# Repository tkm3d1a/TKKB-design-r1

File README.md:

# TKKB-design-r1
 TKm3d1a Keyboard design project, revision 1

MY first attempt at using Github for rev control and publishing of any/all files in KB design.

The Goal is a 60% ish keyboard design, no multiple layout support.  Exposed diodes, with a swapable MCU.

Possibly also add numpad support as I personally use the numpad often.  

Designed to use PCB mount MX style switches.

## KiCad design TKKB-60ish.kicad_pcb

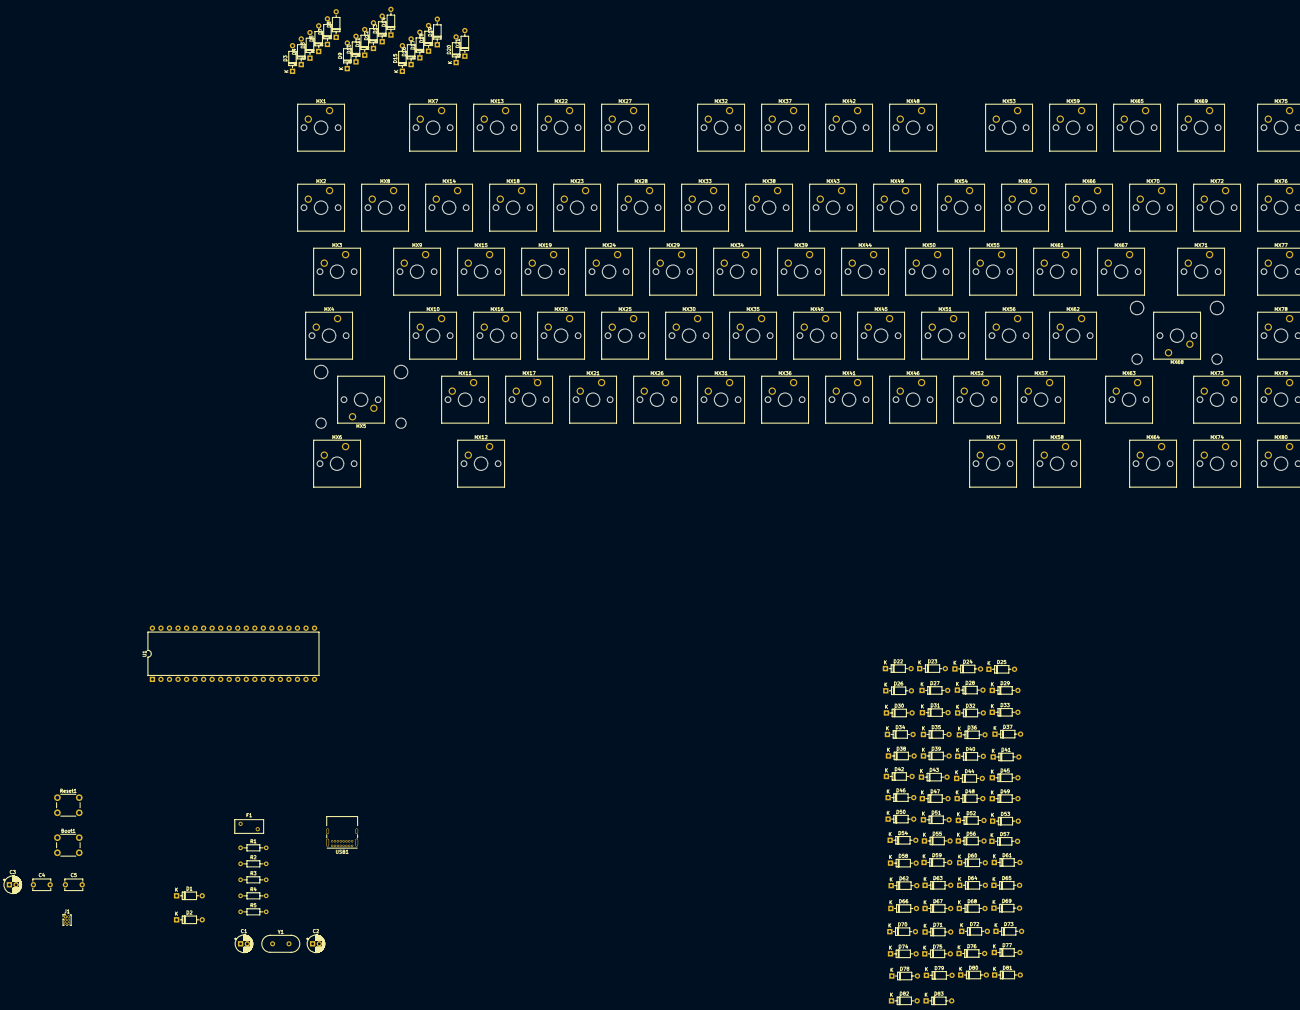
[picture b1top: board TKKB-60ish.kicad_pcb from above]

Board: 2 copper layers, 180 parts (0 on the bottom side), 116 nets.

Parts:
Boot1: Boot; SW_PUSH_6mm
C1, C2: 22p; CP_Radial_D5.0mm_P2.00mm
C3: 4u7; CP_Radial_D5.0mm_P2.00mm
C4, C5: 0u1; C_Disc_D5.1mm_W3.2mm_P5.00mm
D1, D2: 3.6V; D_DO-35_SOD27_P7.62mm_Horizontal
D3, D4, D5, D6, D7, D8, D9, D10, D11, D12, D13, D14, D15, D16, D17, D18, D19, D20, D21, D22, D23, D24, D25, D26, D27, D28, D29, D30, D31, D32, D33, D34, D35, D36, D37, D38, D39, D40, D41, D42, D43, D44, D45, D46, D47, D48, D49, D50, D51, D52, D53, D54, D55, D56, D57, D58, D59, D60, D61, D62, D63, D64, D65, D66, D67, D68, D69, D70, D71, D72, D73, D74, D75, D76, D77, D78, D79, D80, D81, D82, D83: 1N4148TR; D_DO-35_SOD27_P7.62mm_Horizontal
F1: 500mA; Fuse_BelFuse_0ZRE0005FF_L8.3mm_W3.8mm
J1: AVR-ISP-6; PinHeader_2x03_P1.00mm_Vertical
MX1: Esc; SW_Cherry_MX_1.00u_PCB
MX2: Tilde; SW_Cherry_MX_1.00u_PCB
MX3: Tab; SW_Cherry_MX_1.50u_PCB
MX4: Step Caps; SW_Cherry_MX_1.00u_PCB
MX5: Shift; SW_Cherry_MX_2.25u_PCB
MX6: Ctrl; SW_Cherry_MX_1.50u_PCB
MX7: F1; SW_Cherry_MX_1.00u_PCB
MX8: 1; SW_Cherry_MX_1.00u_PCB
MX9: Q; SW_Cherry_MX_1.00u_PCB
MX10: A; SW_Cherry_MX_1.00u_PCB
MX11: Z; SW_Cherry_MX_1.00u_PCB
MX12: Alt; SW_Cherry_MX_1.00u_PCB
MX13: F2; SW_Cherry_MX_1.00u_PCB
MX14: 2; SW_Cherry_MX_1.00u_PCB
MX15: W; SW_Cherry_MX_1.00u_PCB
MX16: S; SW_Cherry_MX_1.00u_PCB
MX17: X; SW_Cherry_MX_1.00u_PCB
MX18: 3; SW_Cherry_MX_1.00u_PCB
MX19: E; SW_Cherry_MX_1.00u_PCB
MX20: D; SW_Cherry_MX_1.00u_PCB
MX21: C; SW_Cherry_MX_1.00u_PCB
MX22: F3; SW_Cherry_MX_1.00u_PCB
MX23: 4; SW_Cherry_MX_1.00u_PCB
MX24: R; SW_Cherry_MX_1.00u_PCB
MX25: F; SW_Cherry_MX_1.00u_PCB
MX26: V; SW_Cherry_MX_1.00u_PCB
MX27: F4; SW_Cherry_MX_1.00u_PCB
MX28: 5; SW_Cherry_MX_1.00u_PCB
MX29: T; SW_Cherry_MX_1.00u_PCB
MX30: G; SW_Cherry_MX_1.00u_PCB
MX31: B; SW_Cherry_MX_1.00u_PCB
MX32: F5; SW_Cherry_MX_1.00u_PCB
MX33: 6; SW_Cherry_MX_1.00u_PCB
MX34: Y; SW_Cherry_MX_1.00u_PCB
MX35: H; SW_Cherry_MX_1.00u_PCB
MX36: N; SW_Cherry_MX_1.00u_PCB
MX37: F6; SW_Cherry_MX_1.00u_PCB
MX38: 7; SW_Cherry_MX_1.00u_PCB
MX39: U; SW_Cherry_MX_1.00u_PCB
MX40: J; SW_Cherry_MX_1.00u_PCB
MX41: M; SW_Cherry_MX_1.00u_PCB
MX42: F7; SW_Cherry_MX_1.00u_PCB
MX43: 8; SW_Cherry_MX_1.00u_PCB
MX44: I; SW_Cherry_MX_1.00u_PCB
MX45: K; SW_Cherry_MX_1.00u_PCB
MX46: <; SW_Cherry_MX_1.00u_PCB
MX47: R Alt; SW_Cherry_MX_1.00u_PCB
MX48: F8; SW_Cherry_MX_1.00u_PCB
MX49: 9; SW_Cherry_MX_1.00u_PCB
MX50: O; SW_Cherry_MX_1.00u_PCB
MX51: L; SW_Cherry_MX_1.00u_PCB
MX52: >; SW_Cherry_MX_1.00u_PCB
MX53: F9; SW_Cherry_MX_1.00u_PCB
MX54: 0; SW_Cherry_MX_1.00u_PCB
MX55: P; SW_Cherry_MX_1.00u_PCB
MX56: ;; SW_Cherry_MX_1.00u_PCB
MX57: /; SW_Cherry_MX_1.00u_PCB
MX58: R Ctrl; SW_Cherry_MX_1.00u_PCB
MX59: F10; SW_Cherry_MX_1.00u_PCB
MX60: -; SW_Cherry_MX_1.00u_PCB
MX61: [; SW_Cherry_MX_1.00u_PCB
MX62: '; SW_Cherry_MX_1.00u_PCB
MX63: RShift; SW_Cherry_MX_1.75u_PCB
MX64: Left Arrow; SW_Cherry_MX_1.00u_PCB
MX65: F11; SW_Cherry_MX_1.00u_PCB
MX66: =; SW_Cherry_MX_1.00u_PCB
MX67: ]; SW_Cherry_MX_1.00u_PCB
MX68: Enter; SW_Cherry_MX_2.25u_PCB
MX69: F12; SW_Cherry_MX_1.00u_PCB
MX70: \; SW_Cherry_MX_1.00u_PCB
MX71: bACKSPACE; SW_Cherry_MX_1.50u_PCB
MX72: Del; SW_Cherry_MX_1.00u_PCB
MX73: Up Arrow; SW_Cherry_MX_1.00u_PCB
MX74: Down Arrow; SW_Cherry_MX_1.00u_PCB
MX75: ?; SW_Cherry_MX_1.00u_PCB
MX76: Home; SW_Cherry_MX_1.00u_PCB
MX77: PgUp; SW_Cherry_MX_1.00u_PCB
MX78: PgDn; SW_Cherry_MX_1.00u_PCB
MX79: End; SW_Cherry_MX_1.00u_PCB
MX80: Right Arrow; SW_Cherry_MX_1.00u_PCB
R1, R2: 5k1; R_Axial_DIN0204_L3.6mm_D1.6mm_P7.62mm_Horizontal
R3: 10k; R_Axial_DIN0204_L3.6mm_D1.6mm_P7.62mm_Horizontal
R4, R5: 75R; R_Axial_DIN0204_L3.6mm_D1.6mm_P7.62mm_Horizontal
Reset1: Reset; SW_PUSH_6mm
U1: ATmega32A-PU; DIP-40_W15.24mm
USB1: Type-C_USB_C_GCT_USB4085; USB_C_Receptacle_GCT_USB4085
Y1: 16MHz; Crystal_HC49-U_Vertical

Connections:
+5V: C3.1, C4.1, C5.1, F1.1, J1.2, R3.1, U1.10, U1.30
/Keyboard Matrix/Col_0: MX1.1, MX2.1, MX3.1, MX4.1, MX5.1, MX6.1, MX7.1, MX8.1, MX9.1, MX10.1, MX11.1, MX12.1
/Keyboard Matrix/Col_1: MX13.1, MX14.1, MX15.1, MX16.1, MX17.1, MX18.1, MX19.1, MX20.1, MX21.1
/Keyboard Matrix/Col_2: MX22.1, MX23.1, MX24.1, MX25.1, MX26.1, MX27.1, MX28.1, MX29.1, MX30.1, MX31.1
/Keyboard Matrix/Col_3: MX32.1, MX33.1, MX34.1, MX35.1, MX36.1, MX37.1, MX38.1, MX39.1, MX40.1, MX41.1
/Keyboard Matrix/Col_4: MX42.1, MX43.1, MX44.1, MX45.1, MX46.1, MX47.1, MX48.1, MX49.1, MX50.1, MX51.1, MX52.1
/Keyboard Matrix/Col_5: MX53.1, MX54.1, MX55.1, MX56.1, MX57.1, MX58.1, MX59.1, MX60.1, MX61.1, MX62.1, MX63.1, MX64.1
/Keyboard Matrix/Col_6: MX65.1, MX66.1, MX67.1, MX68.1, MX69.1, MX70.1, MX71.1, MX73.1, MX74.1, MX78.1, MX79.1, MX80.1
/Keyboard Matrix/Col_7: MX72.1, MX75.1, MX76.1, MX77.1
/Keyboard Matrix/Row_0: D3.1, D15.1, D24.1, D35.1, D45.1, D56.1, D68.1, D78.1
/Keyboard Matrix/Row_1: D9.1, D29.1, D40.1, D51.1, D62.1, D72.1
/Keyboard Matrix/Row_2: D4.1, D16.1, D25.1, D36.1, D46.1, D57.1, D69.1, D75.1
/Keyboard Matrix/Row_3: D10.1, D20.1, D30.1, D41.1, D52.1, D63.1, D73.1, D79.1
/Keyboard Matrix/Row_4: D5.1, D17.1, D26.1, D37.1, D47.1, D58.1, D70.1, D80.1
/Keyboard Matrix/Row_5: D11.1, D21.1, D31.1, D42.1, D53.1, D64.1, D74.1
/Keyboard Matrix/Row_6: D6.1, D18.1, D27.1, D38.1, D48.1, D59.1, D71.1
/Keyboard Matrix/Row_7: D12.1, D22.1, D32.1, D43.1, D54.1, D65.1, D81.1
/Keyboard Matrix/Row_8: D7.1, D19.1, D28.1, D39.1, D49.1, D60.1, D76.1
/Keyboard Matrix/Row_9: D13.1, D23.1, D33.1, D44.1, D55.1, D66.1, D82.1
/Keyboard Matrix/Row_10: D8.1, D50.1, D61.1, D77.1
/Keyboard Matrix/Row_11: D14.1, D34.1, D67.1, D83.1
Boot: Boot1.2, U1.18
D+: R5.1, U1.16
D-: R4.1, U1.17
GND: Boot1.1, C1.2, C2.1, C3.2, C4.2, C5.2, D1.2, D2.2, J1.6, R1.2, R2.2, Reset1.1, U1.11, U1.31, USB1.A1, USB1.A12, USB1.B1, USB1.B12, USB1.S1
MISO: J1.1, U1.7
MOSI: J1.4, U1.6
unnamed: C1.1, U1.13, Y1.1
unnamed: C2.2, U1.12, Y1.2
unnamed: D1.1, R5.2, USB1.A6, USB1.B6
unnamed: D2.1, R4.2, USB1.A7, USB1.B7
unnamed: D3.2, MX1.2
unnamed: D4.2, MX2.2
unnamed: D5.2, MX3.2
unnamed: D6.2, MX4.2
unnamed: D7.2, MX5.2
unnamed: D8.2, MX6.2
unnamed: D9.2, MX7.2
unnamed: D10.2, MX8.2
unnamed: D11.2, MX9.2
unnamed: D12.2, MX10.2
unnamed: D13.2, MX11.2
unnamed: D14.2, MX12.2
unnamed: D15.2, MX13.2
unnamed: D16.2, MX14.2
unnamed: D17.2, MX15.2
unnamed: D18.2, MX16.2
unnamed: D19.2, MX17.2
unnamed: D20.2, MX18.2
unnamed: D21.2, MX19.2
unnamed: D22.2, MX20.2
unnamed: D23.2, MX21.2
unnamed: D24.2, MX22.2
unnamed: D25.2, MX23.2
unnamed: D26.2, MX24.2
unnamed: D27.2, MX25.2
unnamed: D28.2, MX26.2
unnamed: D29.2, MX27.2
unnamed: D30.2, MX28.2
unnamed: D31.2, MX29.2
unnamed: D32.2, MX30.2
unnamed: D33.2, MX31.2
unnamed: D35.2, MX32.2
unnamed: D36.2, MX33.2
unnamed: D37.2, MX34.2
unnamed: D38.2, MX35.2
unnamed: D39.2, MX36.2
unnamed: D40.2, MX37.2
unnamed: D41.2, MX38.2
unnamed: D42.2, MX39.2
unnamed: D43.2, MX40.2
unnamed: D44.2, MX41.2
unnamed: D45.2, MX42.2
unnamed: D46.2, MX43.2
unnamed: D47.2, MX44.2
unnamed: D48.2, MX45.2
unnamed: D49.2, MX46.2
unnamed: D50.2, MX47.2
unnamed: D51.2, MX48.2
unnamed: D52.2, MX49.2
unnamed: D53.2, MX50.2
unnamed: D54.2, MX51.2
unnamed: D55.2, MX52.2
unnamed: D56.2, MX53.2
unnamed: D57.2, MX54.2
unnamed: D58.2, MX55.2
unnamed: D59.2, MX56.2
unnamed: D60.2, MX57.2
unnamed: D61.2, MX58.2
unnamed: D62.2, MX59.2
unnamed: D63.2, MX60.2
unnamed: D64.2, MX61.2
unnamed: D65.2, MX62.2
unnamed: D66.2, MX63.2
unnamed: D67.2, MX64.2
unnamed: D68.2, MX65.2
unnamed: D69.2, MX66.2
unnamed: D70.2, MX67.2
unnamed: D71.2, MX68.2
unnamed: D72.2, MX69.2
unnamed: D73.2, MX70.2
unnamed: D74.2, MX71.2
unnamed: D75.2, MX72.2
unnamed: D76.2, MX73.2
unnamed: D77.2, MX74.2
unnamed: D78.2, MX75.2
unnamed: D79.2, MX76.2
unnamed: D80.2, MX77.2
unnamed: D81.2, MX78.2
unnamed: D82.2, MX79.2
unnamed: D83.2, MX80.2
unnamed: R1.1, USB1.A5
unnamed: R2.1, USB1.B5
Reset: J1.5, R3.2, Reset1.2, U1.9
SCK: J1.3, U1.8
USB_Vbus: F1.2, USB1.A4, USB1.A9, USB1.B4, USB1.B9

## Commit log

2020-12-20 Add Submodules
2020-12-20 Added Plate Raw DXF
2020-12-21 EOD 12-20-20
2020-12-24 LibreCad DXF Edits/Grid Layout
2020-12-24 Schematic Updated - still in work
2020-12-29 Added extra info/URL txt file
2020-12-31 Add Type-c pretty
2020-12-31 Reorg Folder Structure
2021-01-01 Added Row/Col Layout image
2021-01-01 Added USB/Boot/ISP/Init MCU to schematic
2021-01-01 PCB Layout edits
2021-01-02 Updated Schematic
2021-01-02 Begin Cad Files
2021-01-04 update to kicad schematic and pcb
2021-01-12 Added some CAD
2021-01-16 Updated CAD/Added some KiCad Footprints
2021-01-16 Cad updates
2021-01-16 Mopre cad updates(82keys)
2021-01-17 Case r1 Complete
2021-01-17 Quotes added for R1 prototype
2021-02-03 Board layout work
